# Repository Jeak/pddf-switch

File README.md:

# pddf-switch
files for my Pseudo-Doppler Direction-Finding RF switch

Adopted from Morgan State University's RasHAWK RF Switch board, [which is on page 12 of their paper](http://www.geontech.com/download/white_papers/AOC_Challenge_GEON.pdf). Feedback is always welcome!

Parts used*

- ADG904BRUZ x1 (not the -R version although that once works too)
- ADP3330ARTZ-2.5-R7 x1
- TXS0102DCTR x1
- 470pF 0603 SMD caps x2
- 100pF 0603 SMD caps x4

*more detailed bom to come in the future

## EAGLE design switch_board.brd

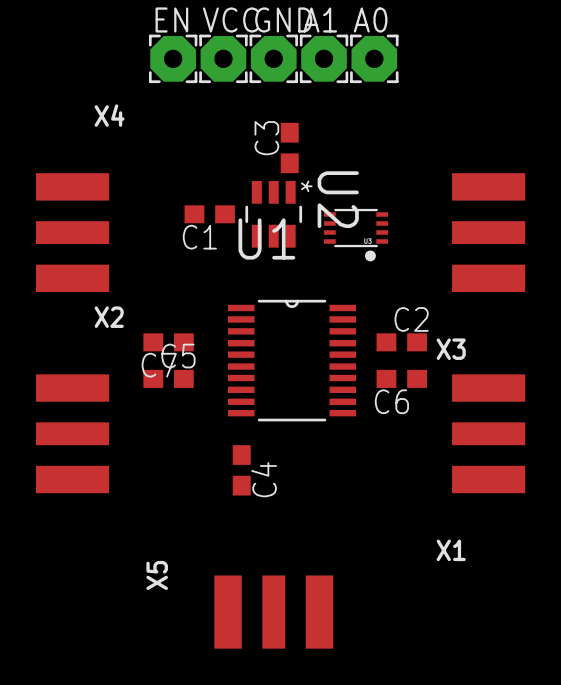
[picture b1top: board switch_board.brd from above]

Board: 2 copper layers, 20 parts (0 on the bottom side), 18 nets, no tracks yet.

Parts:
A0, A1: 2,54/1,0
C1, C3: 0.47uF; C0603
C2, C4, C5, C6, C7: 0.1uF; C0603
EN: 2,54/1,0
GND: 2,54/1,0
U1: ADG904BRUZ; SOP65P640X120-20N
U2: ADP3330ARTZ-2.5-R7; SOT95P280X145-6N
U3: VFSOP-8
VCC: 2,54/1,0
X1, X2, X3, X4, X5: SMA_EDGELAUNCH

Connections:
A0_LVTTL: U1.20, U3.P$5
A0_TTL: A0.1, U3.P$8
A1_LVTTL: U1.19, U3.P$4
A1_TTL: A1.1, U3.P$1
GND: C1.2, C3.2, GND.1, U1.1, U1.3, U1.5, U1.6, U1.8, U1.9, U1.11, U1.12, U1.13, U1.15, U1.16, U1.18, U2.4, U3.P$2, X1.GND@1, X1.GND@2, X1.GND@3, X1.GND@4, X2.GND@1, X2.GND@2, X2.GND@3, X2.GND@4, X3.GND@1, X3.GND@2, X3.GND@3, X3.GND@4, X4.GND@1, X4.GND@2, X4.GND@3, X4.GND@4, X5.GND@1, X5.GND@2, X5.GND@3, X5.GND@4
unnamed: EN.1, U2.6
unnamed: C1.1, U2.2, U3.P$7, VCC.1
unnamed: C5.1, X2.P
unnamed: C4.1, U1.10
unnamed: C2.1, U1.17
unnamed: C3.1, U1.2, U2.1, U3.P$3
unnamed: C2.2, X3.P
unnamed: C7.2, X4.P
unnamed: C6.1, X1.P
RF1: C7.1, U1.4
RF3: C5.2, U1.7
RF4: C6.2, U1.14
RFC: C4.2, X5.P

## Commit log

2017-08-23 :neckbeard: Added .gitattributes & .gitignore files
2017-08-23 Import files!
2017-08-23 Changed Readme
2017-08-26 Add DC Blocking Caps
    Added 100uf caps for dc blocking on rf lines. Also updated readme
2017-08-30 Switched to Altium
    had a change of heart and changed board design software (with a blank
    slate)
